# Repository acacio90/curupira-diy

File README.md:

<div align="center">

  # CURUPIRA

  **Dispositivo portátil estilo Cardputer rodando [Bruce](https://github.com/BruceDevices/firmware) — ESP32-S3, feito pra montar à mão (THT).**
</div>

---

## O que é

CURUPIRA é uma PCB DIY, inspirada no M5Stack Cardputer, projetada no **KiCad** para rodar o firmware **Bruce** num **ESP32-S3-DevKitC-1 (N16R8)**. O foco é um "canivete suíço" de RF/pentest de estudo, **soldável à mão** (componentes through-hole + DevKit encaixável, sem SMD).

> ⚠️ **Uso educacional / laboratório próprio.** Rádio e RF têm regras legais — use só em equipamentos e redes seus, para estudo.

## Recursos

| Bloco | Hardware | Conector |
|---|---|---|
| Cérebro | ESP32-S3-DevKitC-1 N16R8 (WiFi + BLE nativos) | U1 |
| Tela | ST7789 SPI (IPS) | J1 |
| Sub-GHz | CC1101 (433 MHz) | J3 |
| 2.4 GHz | NRF24L01+PA+LNA | J9 |
| NFC/RFID | PN532 (I2C) | J2 |
| Armazenamento | microSD (SPI, 3,3 V) | J4 |
| Infravermelho | TSOP38238 (RX) + 2× LED IR 940 nm (TX) | U2/D3/D5 |
| Teclado | M5Stack CardKB (I2C) | J8 |
| GPS (opcional) | NEO-6M / NEO-M8N (UART) | J6 |
| Energia | TP4056 (USB-C) + LiPo 3,7 V | J5 |
| Entrada | 4 botões (Prev/Sel/Next/Esc) + chave liga/desliga | SW1–SW5 |

## Estado do projeto

- **v0.4.1** — placa 100×100 mm (2 camadas), 4 furos M3, **roteada e com DRC limpo** (0 violações). Gerbers em `production/curupira-v0.4.1-gerbers-jlcpcb.zip`.
- **v0.4.1 (correção):** removida 1 via de GND que ficava sobre o furo do J9-1 (furos sobrepostos), texto "PN532" afastado do J2 e serigrafia com a versão atualizada. DRC só com os 2 avisos esperados da serigrafia do DevKit na borda.
- **Novidades da v0.4:** buzzer removido (libera o GPIO3), **2 emissores de IR** (D3+D5 nos cantos de cima, mais alcance/cobertura), re-posicionamento dos componentes e **re-roteamento completo**, plano de GND costurado com vias de stitching, microSD remapeado p/ módulo 3,3 V.
- **Ainda não fabricada** — plano: validar na **protoboard** antes de mandar fazer → [plano de teste](docs/TESTE_PROTOBOARD.md) (versão interativa: `docs/teste-protoboard.html`).

## Renders

Para atualizar depois de mexer na placa ou no esquemático: `./renders/gerar.sh`

## Estrutura

```bash
git clone git@github.com:acacio90/curupira-diy.git
```

```
curupira-diy.kicad_pro / .kicad_sch / .kicad_pcb   → projeto KiCad
GUIA.md                 → mapa de pinos (GPIO ↔ cada conector)
production/             → Gerbers v0.4.1 (JLCPCB), BOM (bom.csv), lista de compras
renders/                → renders atuais da placa e do esquemático (gerar.sh recria tudo)
3d/                     → modelos 3D de todos os módulos e peças (ver 3d/LEIA-ME.md)
lib/                    → biblioteca local da Espressif (símbolo + footprint do DevKit)
docs/pinagem.html       → diagrama interativo da pinagem do ESP32 (abrir no navegador)
docs/TESTE_PROTOBOARD.md → plano de teste bloco a bloco na protoboard, antes de fabricar
docs/teste-protoboard.html → o mesmo plano como manual interativo (protoboard desenhada passo a passo)
arte/                   → logo CURUPIRA: rosto colorido (README), rosto e corpo em P&B (serigrafia), versões transparentes
production/LISTA_DE_COMPRAS.md → lista de compras com links e preços
```

## Como fabricar

1. Envie `production/curupira-v0.4.1-gerbers-jlcpcb.zip` para a JLCPCB (2 camadas, 1,6 mm, HASL).
2. Compre as peças pela `production/LISTA_DE_COMPRAS.md`.
3. Solde os THT à mão; encaixe o DevKit nas barras fêmea.
4. Confira continuidade **3V3 ↔ GND** com multímetro **antes** de ligar.

## Créditos

- Firmware: **Bruce** (BruceDevices / pr3y e colaboradores).
- Projeto de hardware: CURUPIRA.

## Licença

A definir (sugestão: hardware em **CERN-OHL-S**, docs em **CC BY-SA 4.0**).

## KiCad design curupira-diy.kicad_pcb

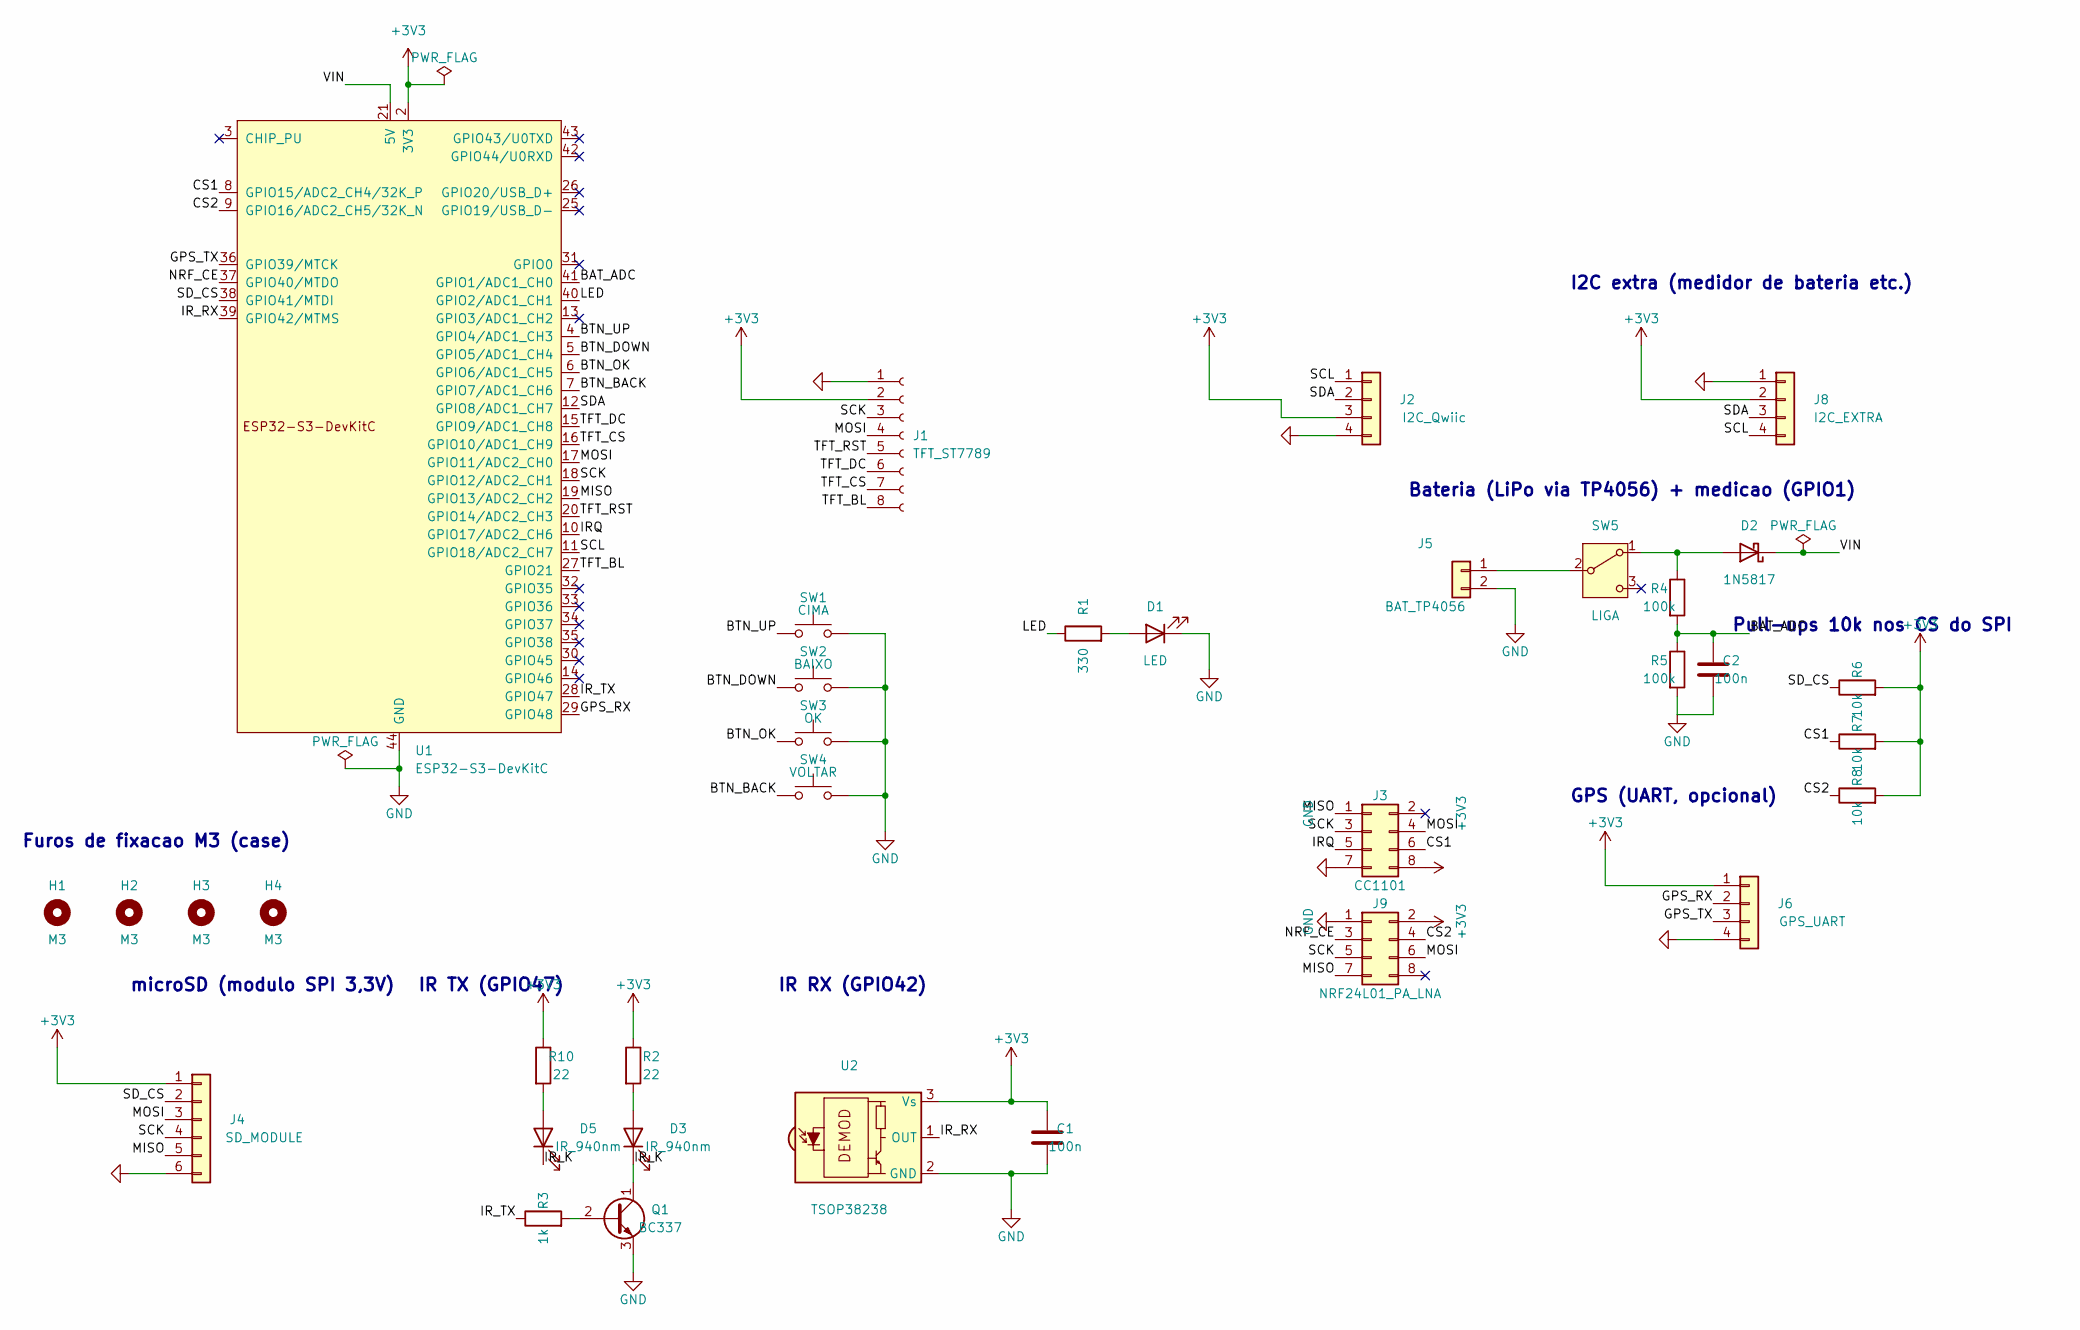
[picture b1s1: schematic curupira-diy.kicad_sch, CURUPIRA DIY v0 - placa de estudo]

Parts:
C1, C2: 100n; C_Disc_D3.0mm_W1.6mm_P2.50mm
D1: LED; LED_D3.0mm
D2: 1N5817; D_DO-41_SOD81_P10.16mm_Horizontal
D3, D5: IR_940nm; LED_D5.0mm
H1, H2, H3, H4: M3; MountingHole_3.2mm_M3
J1: TFT_ST7789; PinSocket_1x08_P2.54mm_Vertical
J2: I2C_Qwiic; PinSocket_1x04_P2.54mm_Vertical
J3: CC1101; PinSocket_2x04_P2.54mm_Vertical
J4: SD_MODULE; PinSocket_1x06_P2.54mm_Vertical
J5: BAT_TP4056; PinHeader_1x02_P2.54mm_Vertical
J6: GPS_UART; PinSocket_1x04_P2.54mm_Vertical
J8: I2C_EXTRA; PinSocket_1x04_P2.54mm_Vertical
J9: NRF24L01_PA_LNA; PinSocket_2x04_P2.54mm_Vertical
Q1: BC337; TO-92_Inline
R1: 330; R_Axial_DIN0207_L6.3mm_D2.5mm_P7.62mm_Horizontal
R2, R10: 22; R_Axial_DIN0207_L6.3mm_D2.5mm_P7.62mm_Horizontal
R3: 1k; R_Axial_DIN0207_L6.3mm_D2.5mm_P7.62mm_Horizontal
R4, R5: 100k; R_Axial_DIN0207_L6.3mm_D2.5mm_P7.62mm_Horizontal
R6, R7, R8: 10k; R_Axial_DIN0207_L6.3mm_D2.5mm_P7.62mm_Horizontal
SW1: CIMA; SW_PUSH_6mm
SW2: BAIXO; SW_PUSH_6mm
SW3: OK; SW_PUSH_6mm
SW4: VOLTAR; SW_PUSH_6mm
SW5: LIGA; SW_Slide_SPDT_Straight_CK_OS102011MS2Q
U1: ESP32-S3-DevKitC
U2: TSOP38238; Vishay_MINICAST-3Pin

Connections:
+3V3: C1.1, J1.2, J2.3, J3.8, J4.1, J6.1, J8.2, J9.2, R2.1, R6.2, R7.2, R8.2, R10.1, U1.1 (3V3), U1.2 (3V3), U2.3 (Vs)
/BAT_ADC: C2.1, R4.2, R5.1, U1.41 (GPIO1/ADC1_CH0)
/BTN_BACK: SW4.1, U1.7 (GPIO7/ADC1_CH6)
/BTN_DOWN: SW2.1, U1.5 (GPIO5/ADC1_CH4)
/BTN_OK: SW3.1, U1.6 (GPIO6/ADC1_CH5)
/BTN_UP: SW1.1, U1.4 (GPIO4/ADC1_CH3)
/CS1: J3.6, R7.1, U1.8 (GPIO15/ADC2_CH4/32K_P)
/CS2: J9.4, R8.1, U1.9 (GPIO16/ADC2_CH5/32K_N)
/GPS_RX: J6.2, U1.29 (GPIO48)
/GPS_TX: J6.3, U1.36 (GPIO39/MTCK)
/IRQ: J3.5, U1.10 (GPIO17/ADC2_CH6)
/IR_K: D3.1 (K), D5.1 (K), Q1.1 (C)
/IR_RX: U1.39 (GPIO42/MTMS), U2.1 (OUT)
/IR_TX: R3.1, U1.28 (GPIO47)
/LED: R1.1, U1.40 (GPIO2/ADC1_CH1)
/MISO: J3.1, J4.5, J9.7, U1.19 (GPIO13/ADC2_CH2)
/MOSI: J1.4, J3.4, J4.3, J9.6, U1.17 (GPIO11/ADC2_CH0)
/NRF_CE: J9.3, U1.37 (GPIO40/MTDO)
/SCK: J1.3, J3.3, J4.4, J9.5, U1.18 (GPIO12/ADC2_CH1)
/SCL: J2.1, J8.4, U1.11 (GPIO18/ADC2_CH7)
/SDA: J2.2, J8.3, U1.12 (GPIO8/ADC1_CH7)
/SD_CS: J4.2, R6.1, U1.38 (GPIO41/MTDI)
/TFT_BL: J1.8, U1.27 (GPIO21)
/TFT_CS: J1.7, U1.16 (GPIO10/ADC1_CH9)
/TFT_DC: J1.6, U1.15 (GPIO9/ADC1_CH8)
/TFT_RST: J1.5, U1.20 (GPIO14/ADC2_CH3)
/VIN: D2.1 (K), U1.21 (5V)
GND: C1.2, C2.2, D1.1 (K), J1.1, J2.4, J3.7, J4.6, J5.2, J6.4, J8.1, J9.1, Q1.3 (E), R5.2, SW1.2, SW2.2, SW3.2, SW4.2, U1.22 (GND), U1.23 (GND), U1.24 (GND), U1.44 (GND), U2.2 (GND)
unnamed: D1.2 (A), R1.2
unnamed: D2.2 (A), R4.1, SW5.1 (A)
unnamed: D3.2 (A), R2.2
unnamed: D5.2 (A), R10.2
unnamed: J5.1, SW5.2 (B)
unnamed: Q1.2 (B), R3.2

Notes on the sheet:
microSD (modulo SPI 3,3V)
IR TX (GPIO47)
IR RX (GPIO42)
Bateria (LiPo via TP4056) + medicao (GPIO1)
GPS (UART, opcional)
I2C extra (medidor de bateria etc.)
Furos de fixacao M3 (case)
Pull-ups 10k nos CS do SPI

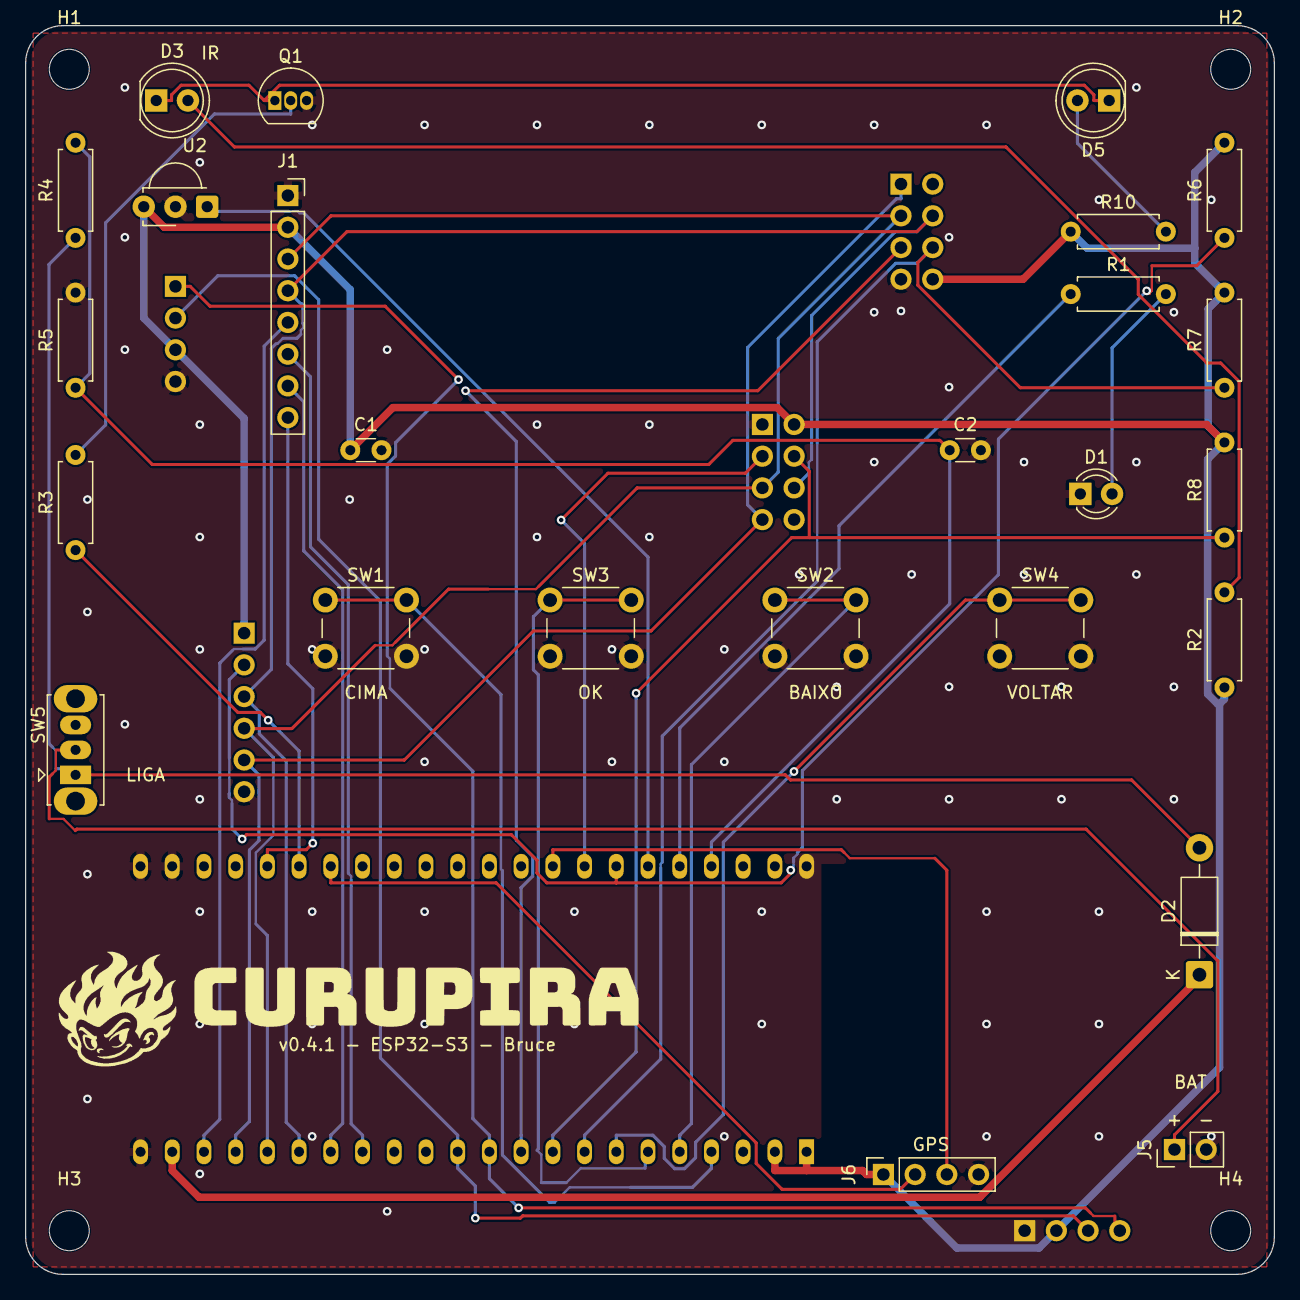
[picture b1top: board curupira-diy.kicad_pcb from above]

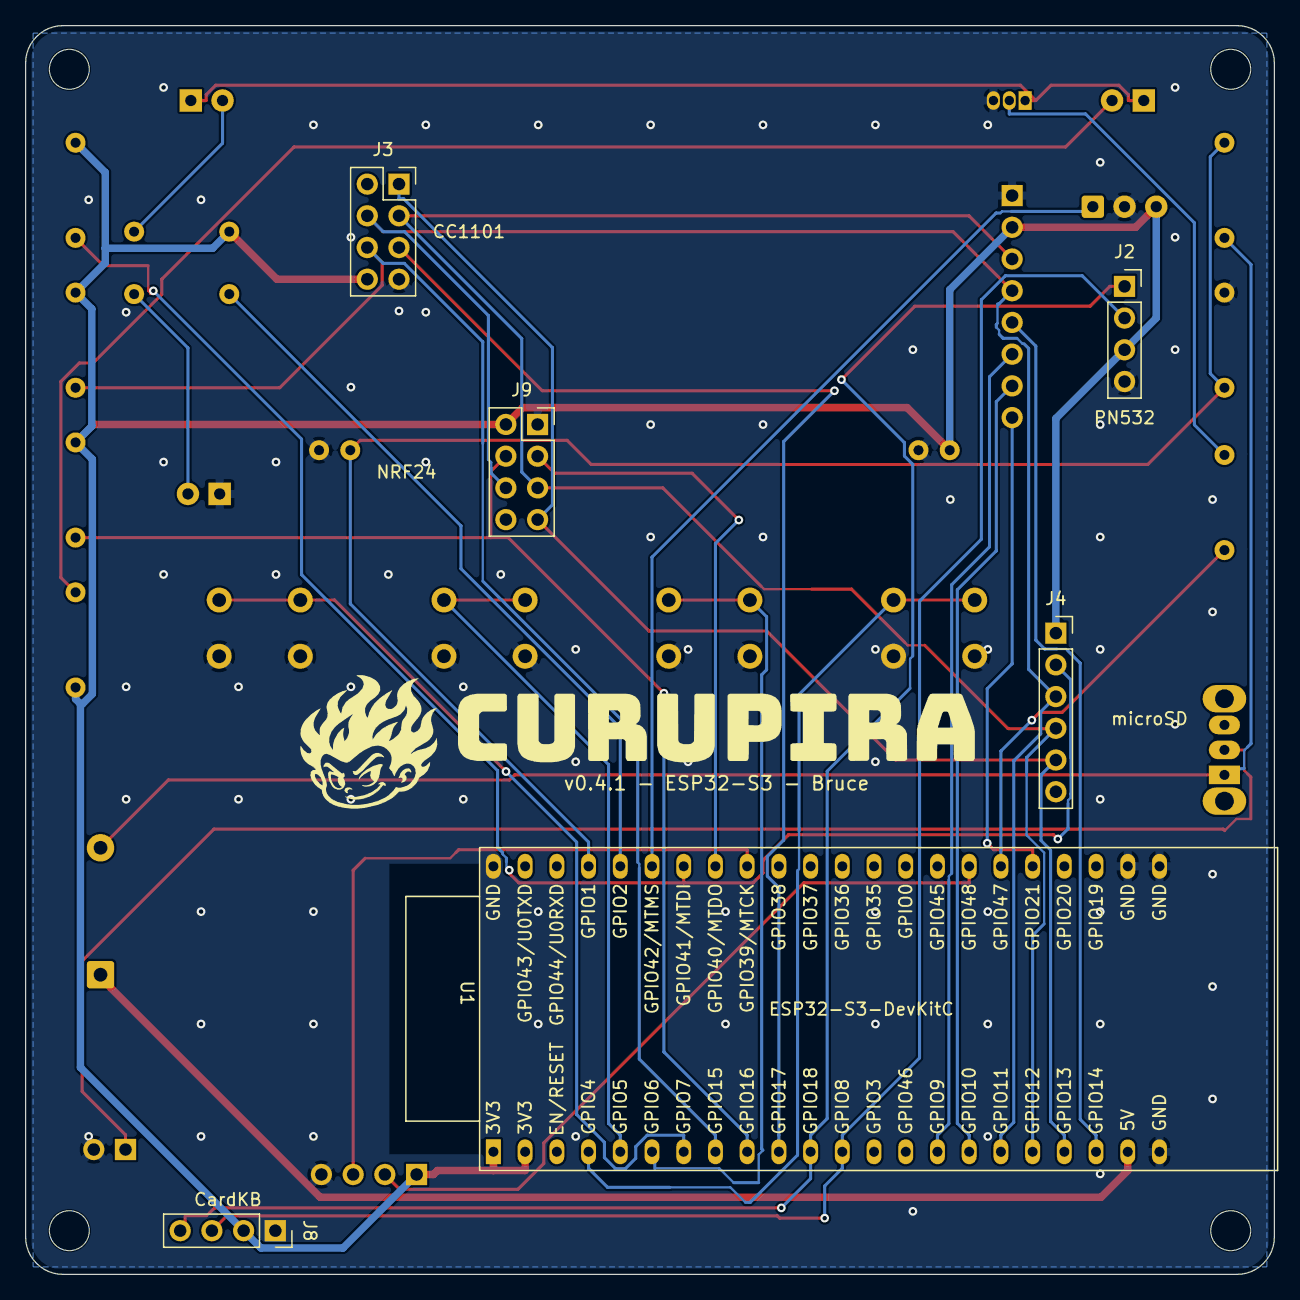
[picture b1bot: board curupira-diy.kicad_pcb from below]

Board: 2 copper layers, 100.0 x 100.0 mm, 35 parts (6 on the bottom side), 34 nets.

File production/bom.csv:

"Reference","Value","Footprint","QUANTITY"
"C1,C2","100n","Capacitor_THT:C_Disc_D3.0mm_W1.6mm_P2.50mm","2"
"D1","LED","LED_THT:LED_D3.0mm","1"
"D2","1N5817","Diode_THT:D_DO-41_SOD81_P10.16mm_Horizontal","1"
"D3,D5","IR_940nm","LED_THT:LED_D5.0mm","2"
"J1","TFT_ST7789","Connector_PinSocket_2.54mm:PinSocket_1x08_P2.54mm_Vertical","1"
"J2","I2C_Qwiic","Connector_PinSocket_2.54mm:PinSocket_1x04_P2.54mm_Vertical","1"
"J3","CC1101","Connector_PinSocket_2.54mm:PinSocket_2x04_P2.54mm_Vertical","1"
"J4","SD_MODULE","Connector_PinSocket_2.54mm:PinSocket_1x06_P2.54mm_Vertical","1"
"J5","BAT_TP4056","Connector_PinHeader_2.54mm:PinHeader_1x02_P2.54mm_Vertical","1"
"J6","GPS_UART","Connector_PinSocket_2.54mm:PinSocket_1x04_P2.54mm_Vertical","1"
"J8","I2C_EXTRA","Connector_PinSocket_2.54mm:PinSocket_1x04_P2.54mm_Vertical","1"
"J9","NRF24L01_PA_LNA","Connector_PinSocket_2.54mm:PinSocket_2x04_P2.54mm_Vertical","1"
"Q1","BC337","Package_TO_SOT_THT:TO-92_Inline","1"
"R1","330","Resistor_THT:R_Axial_DIN0207_L6.3mm_D2.5mm_P7.62mm_Horizontal","1"
"R2,R10","22","Resistor_THT:R_Axial_DIN0207_L6.3mm_D2.5mm_P7.62mm_Horizontal","2"
"R3","1k","Resistor_THT:R_Axial_DIN0207_L6.3mm_D2.5mm_P7.62mm_Horizontal","1"
"R4,R5","100k","Resistor_THT:R_Axial_DIN0207_L6.3mm_D2.5mm_P7.62mm_Horizontal","2"
"R6-R8","10k","Resistor_THT:R_Axial_DIN0207_L6.3mm_D2.5mm_P7.62mm_Horizontal","3"
"SW1","CIMA","Button_Switch_THT:SW_PUSH_6mm","1"
"SW2","BAIXO","Button_Switch_THT:SW_PUSH_6mm","1"
"SW3","OK","Button_Switch_THT:SW_PUSH_6mm","1"
"SW4","VOLTAR","Button_Switch_THT:SW_PUSH_6mm","1"
"SW5","LIGA","Button_Switch_THT:SW_Slide_SPDT_Straight_CK_OS102011MS2Q","1"
"U1","ESP32-S3-DevKitC","PCM_Espressif:ESP32-S3-DevKitC","1"
"U2","TSOP38238","OptoDevice:Vishay_MINICAST-3Pin","1"
